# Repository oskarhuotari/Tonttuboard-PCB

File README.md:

A carrier board for a Teensy 4.0 made for the 2026 Finnish CanSat competition.

---
The board includes:
- Holes for the Teensy 4.0
- ICM-40609-D (IMU)
- BMP388 (Barometer)
- W25Q256JVFIQT (Flash Chip)
- LDR holes
- Thermistor holes
- PMW cable holes
- cool graphics
---
Insturctions:
- Buy a teensy 4.0 and order this PCB from JLCPCB
- Solder them together
- Use Tonttulib (or make your own libs for the sensors)
- Fly your project
- Cry

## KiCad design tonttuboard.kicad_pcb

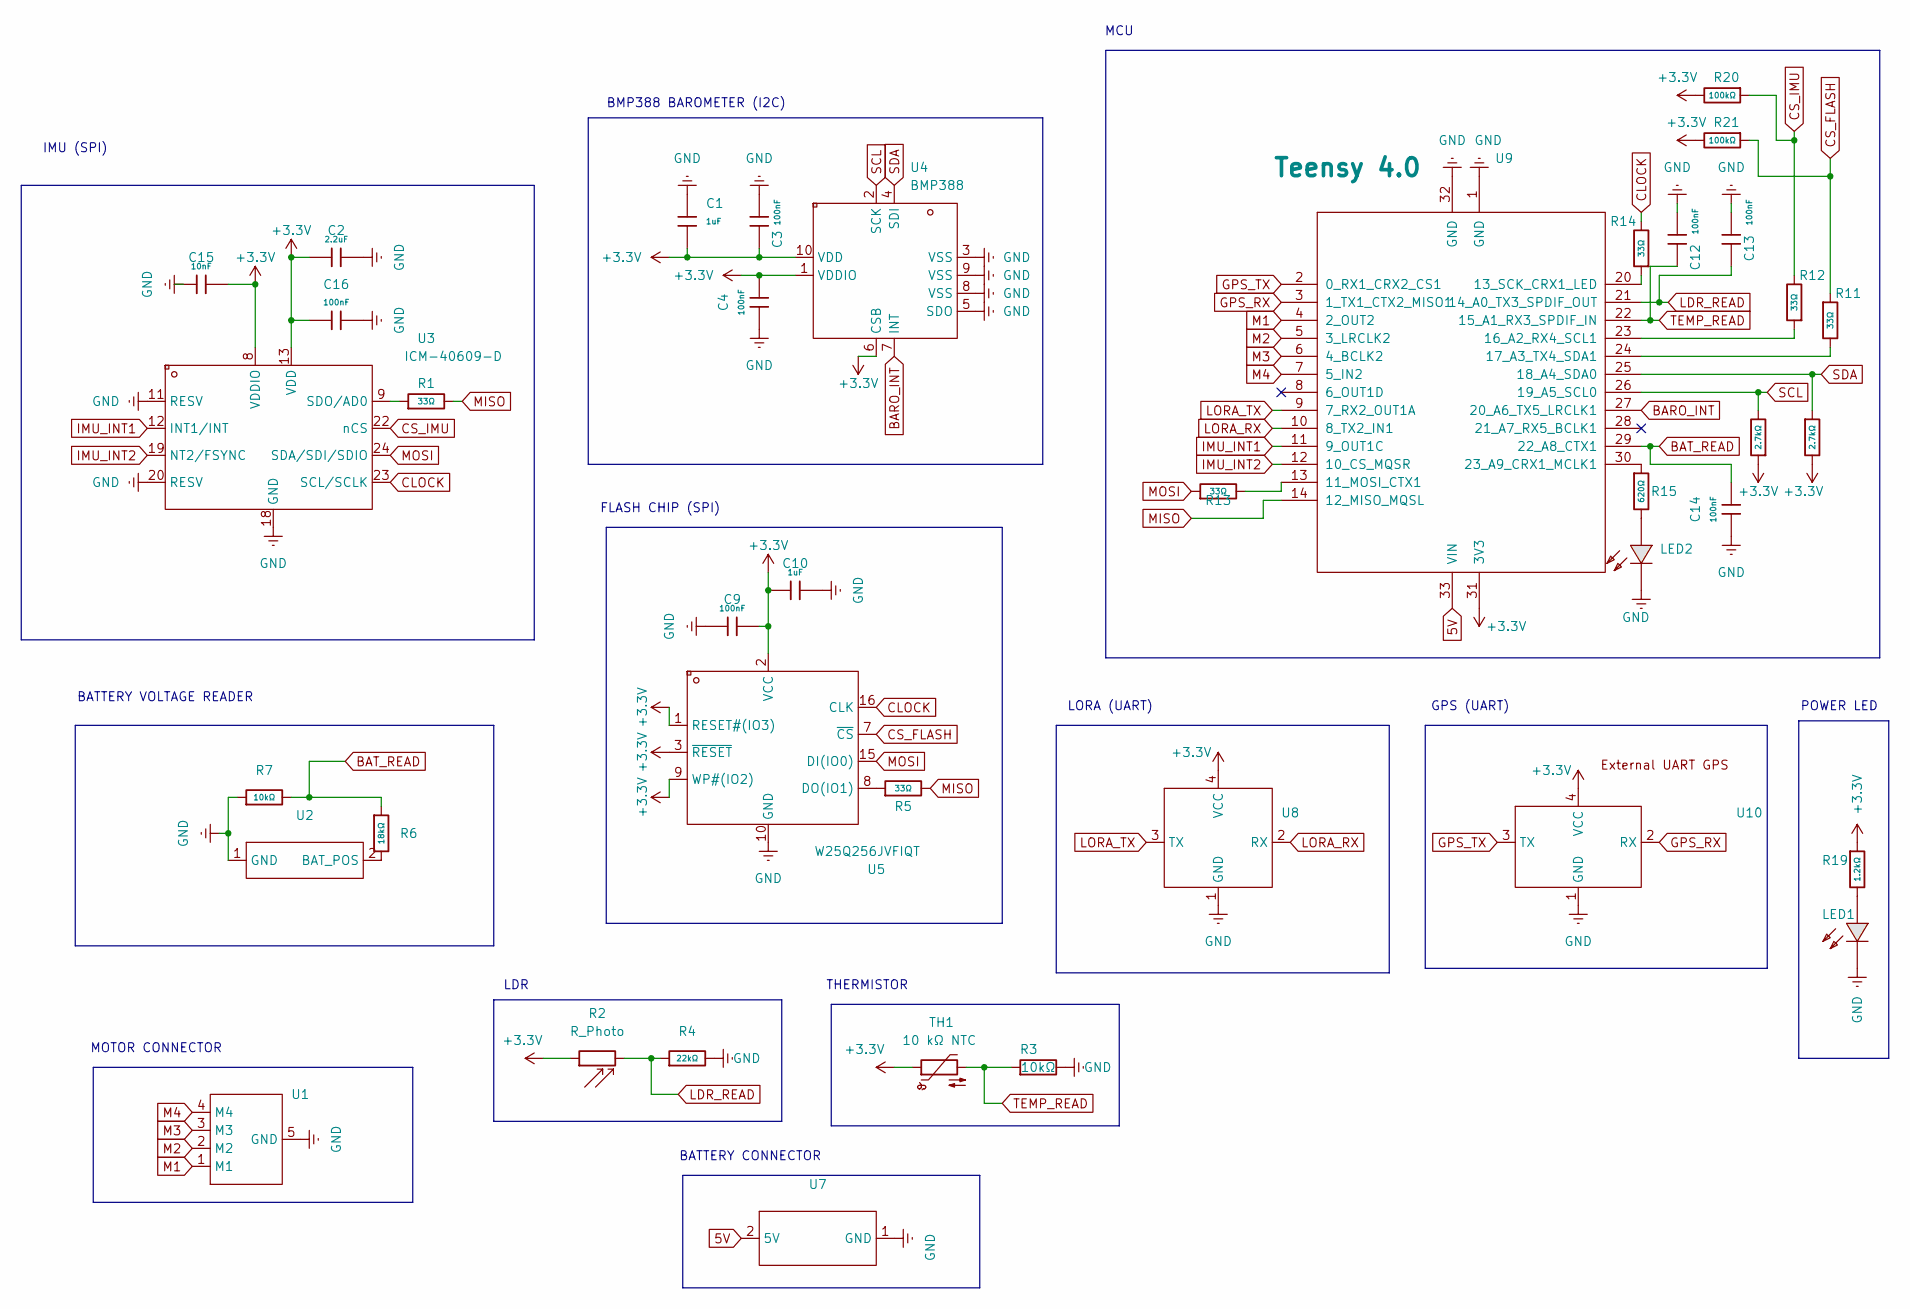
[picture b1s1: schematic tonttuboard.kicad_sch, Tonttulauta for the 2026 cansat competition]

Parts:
C1, C10: 1uF; C_0603; Voltage Rated 50V; Tolerance ±10%; Part CL10A105KB8NNNC; LCSC C15849
C2: 2.2uF; C_0603; Voltage Rated 16V; Tolerance ±10%; Part CL10A225KO8NNNC; LCSC C23630
C3, C4, C9, C12, C13, C14, C16: 100nF; C_0603; Voltage Rated 50V; Tolerance ±10%; Part CC0603KRX7R9BB104; LCSC C14663
C15: 10nF; C_0603; Voltage Rated 50V; Tolerance ±10%; Part 0603B103K500NT; LCSC C57112
LED1: FC-DA1608HRK-620D; LED0603-RD_RED; LCSC Part C84263
LED2: FC-D1608UGK-520D10; LED0603-RD_1; LCSC Part C84267
R1, R5, R11, R12, R13, R14: 33Ω; R_0603; Tolerance ±1%; LCSC Part C108661
R2: R_Photo; LDR-holes
R3: 0603WAF1002T5E; R_0603; Overload Voltage (Max) 75V; Tolerance ±1%; Part 0603WAF1002T5E; LCSC Part C25804
R4: 22kΩ; R_0603; Overload Voltage (Max) 75V; Tolerance ±1%; Part 0603WAF2202T5E; LCSC C31850
R6: 18kΩ; R_0603; Overload Voltage (Max) 75V; Tolerance ±1%; Part 0603WAF1802T5E; LCSC C25810
R7: 10kΩ; R_0603; Overload Voltage (Max) 75V; Tolerance ±1%; Part 0603WAF1002T5E; LCSC C25804
R15: 620Ω; R_0603; Overload Voltage (Max) 75V; Tolerance ±1%; Part 0603WAF6200T5E; LCSC C23220
R16, R17: 2.7kΩ; R_0603; LCSC Part C13167
R19: 1.2kΩ; R_0603; Overload Voltage (Max) 75V; Tolerance ±1%; Part 0603WAF1201T5E; LCSC C22765
R20, R21: 100kΩ; R_0603; Overload Voltage (Max) 75V; Tolerance ±1%; Part 0603WAF1003T5E; LCSC Part C25803
TH1: 10 kΩ NTC; Thermistor-holes
U1: Motor-connector
U2: Voltage-read
U3: ICM-40609-D; LGA-24_L3.0-W3.0-P0.40-TL; LCSC Part C5360621
U4: BMP388; SENSORM-SMD_BMP388; LCSC Part C779278
U5: W25Q256JVFIQT; SOIC-16_L10.3-W7.5-P1.27-LS10.3-BL; LCSC Part C779876
U7: Battery-connector
U8, U10: UART-connector
U9: Teensy 4.0; Teensy40

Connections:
5V: U7.2 (5V), U9.33 (VIN)
+3.3V: C1.2, C2.1, C3.1, C4.2, C9.2, C10.1, C15.2, C16.1, R2.1, R16.1, R17.2, R19.1, R20.2, R21.2, TH1.1, U3.8 (VDDIO), U3.13 (VDD), U4.1 (VDDIO), U4.6 (CSB), U4.10 (VDD), U5.1 (RESET#(IO3)), U5.2 (VCC), U5.3 (~RESET), U5.9 (WP#(IO2)), U8.4 (VCC), U9.31 (3V3), U10.4 (VCC)
BARO_INT: U4.7 (INT), U9.27 (20_A6_TX5_LRCLK1)
BAT_READ: C14.2, R6.1, R7.2, U9.29 (22_A8_CTX1)
CLOCK: R14.2, U3.23 (SCL/SCLK), U5.16 (CLK)
CS_FLASH: R11.1, R21.1, U5.7 (~CS)
CS_IMU: R12.2, R20.1, U3.22 (nCS)
GND: C1.1, C2.2, C3.2, C4.1, C9.1, C10.2, C12.2, C13.2, C14.1, C15.1, C16.2, LED1.1 (K), LED2.1 (K), R3.2, R4.2, R7.1, U1.5 (GND), U2.1 (GND), U3.11 (RESV), U3.18 (GND), U3.20 (RESV), U4.3 (VSS), U4.5 (SDO), U4.8 (VSS), U4.9 (VSS), U5.10 (GND), U7.1 (GND), U8.1 (GND), U9.1 (GND), U9.32 (GND), U10.1 (GND)
GPS_RX: U9.3 (1_TX1_CTX2_MISO1), U10.2 (RX)
GPS_TX: U9.2 (0_RX1_CRX2_CS1), U10.3 (TX)
IMU_INT1: U3.12 (INT1/INT), U9.11 (9_OUT1C)
IMU_INT2: U3.19 (NT2/FSYNC), U9.12 (10_CS_MQSR)
LDR_READ: C13.1, R2.2, R4.1, U9.21 (14_A0_TX3_SPDIF_OUT)
LORA_RX: U8.2 (RX), U9.10 (8_TX2_IN1)
LORA_TX: U8.3 (TX), U9.9 (7_RX2_OUT1A)
M1: U1.1 (M1), U9.4 (2_OUT2)
M2: U1.2 (M2), U9.5 (3_LRCLK2)
M3: U1.3 (M3), U9.6 (4_BCLK2)
M4: U1.4 (M4), U9.7 (5_IN2)
MISO: R1.2, R5.2, U9.14 (12_MISO_MQSL)
MOSI: R13.1, U3.24 (SDA/SDI/SDIO), U5.15 (DI(IO0))
unnamed: LED1.2 (A), R19.2
unnamed: LED2.2 (A), R15.2
unnamed: R6.2, U2.2 (BAT_POS)
unnamed: R1.1, U3.9 (SDO/AD0)
unnamed: R5.1, U5.8 (DO(IO1))
unnamed: R13.2, U9.13 (11_MOSI_CTX1)
unnamed: R14.1, U9.20 (13_SCK_CRX1_LED)
unnamed: R12.1, U9.23 (16_A2_RX4_SCL1)
unnamed: R11.2, U9.24 (17_A3_TX4_SDA1)
unnamed: R15.1, U9.30 (23_A9_CRX1_MCLK1)
SCL: R16.2, U4.2 (SCK), U9.26 (19_A5_SCL0)
SDA: R17.1, U4.4 (SDI), U9.25 (18_A4_SDA0)
TEMP_READ: C12.1, R3.1, TH1.2, U9.22 (15_A1_RX3_SPDIF_IN)

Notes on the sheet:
BMP388 BAROMETER (I2C)
LORA (UART)
BATTERY CONNECTOR
IMU (SPI)
THERMISTOR
FLASH CHIP (SPI)
MCU
BATTERY VOLTAGE READER
GPS (UART)
LDR
POWER LED
MOTOR CONNECTOR

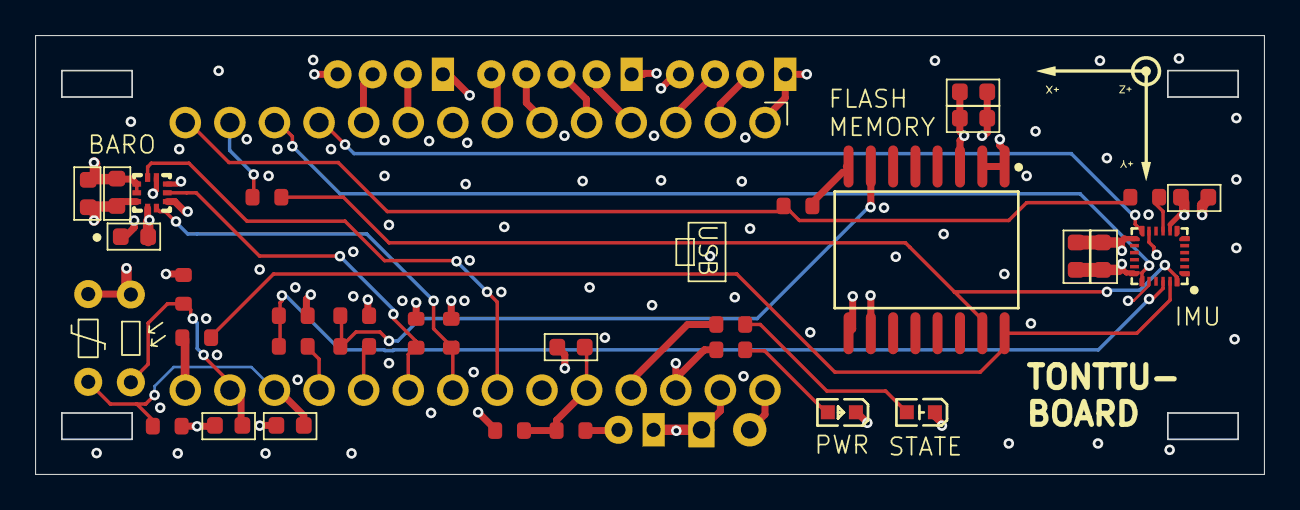
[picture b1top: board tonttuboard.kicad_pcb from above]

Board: 4 copper layers, 70.0 x 25.0 mm, 40 parts (0 on the bottom side), 34 nets.

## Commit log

2025-12-18 Tonttuboard inital commit
2025-12-18 Made a netclass for power.
2025-12-18 Improved component placement
2025-12-20 Routed signals
2025-12-21 Added gnd vias and decorated
2025-12-21 Improved clearances and silkscreen, added copper fill on l4 and vias
2025-12-21 Add README for Teensy 4.0 carrier board project
    Added project description and component list for the Teensy 4.0 carrier board.
2025-12-23 Replaced LDR with a through hole due to a soldering temperature issue. Also made the thermistor silk screen better and fixed a typo. Added CanSat 2026 Vaasa text to the back silkscreen
2025-12-23 Added a few footprints
2026-01-18 Changed the CS Magnetometer 100 kohm pull-up to 4.7 kohm pulldown
2026-03-29 Removed magnetometer and changed component placement
